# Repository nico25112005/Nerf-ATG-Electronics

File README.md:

# Nerf-ATG-Electronics

This repository contains the electronic design files for a custom printed circuit board (PCB) developed to enhance Nerf LaserOps blasters. The board utilizes an ESP32-S3 microcontroller to manage the blaster's functions and communicate via Bluetooth with a Unity application.

## Features

- Custom PCB design for Nerf LaserOps blasters
- ESP32-S3 microcontroller for improved performance and connectivity
- Bluetooth Classic for communication with a Unity application

## Installation

1. **PCB Assembly:**

   - Solder the components onto the board as per the schematic and Bill of Materials (BOM).

2. **Firmware Flashing:**

   - Flash the firmware onto the ESP32-S3. The firmware can be found in the Nerf-ATG-Firmware repository.

3. **Integration:**

   - Replace the original mainboard in the Nerf LaserOps blaster with the custom PCB.

4. **Unity App Setup:**

   - Install the Unity app from the Nerf-ATG-App repository on your device.
   - Pair the blaster with the app via Bluetooth.

## Usage

1. **Power On:**

   - Turn on the blaster.

2. **Connect to App:**

   - Open the Unity app and connect to the blaster via Bluetooth.

3. **Operation:**

   - Use the app to control and monitor the blaster’s functions.

## Contributing

Contributions are welcome! We are currently seeking assistance with programming the ESP32. If you have experience with ESP32 development, please consider contributing to the Nerf-ATG-Firmware repository. Please fork the repository and submit a pull request with your changes.

## Contact

For questions or support, please contact nico25112005.

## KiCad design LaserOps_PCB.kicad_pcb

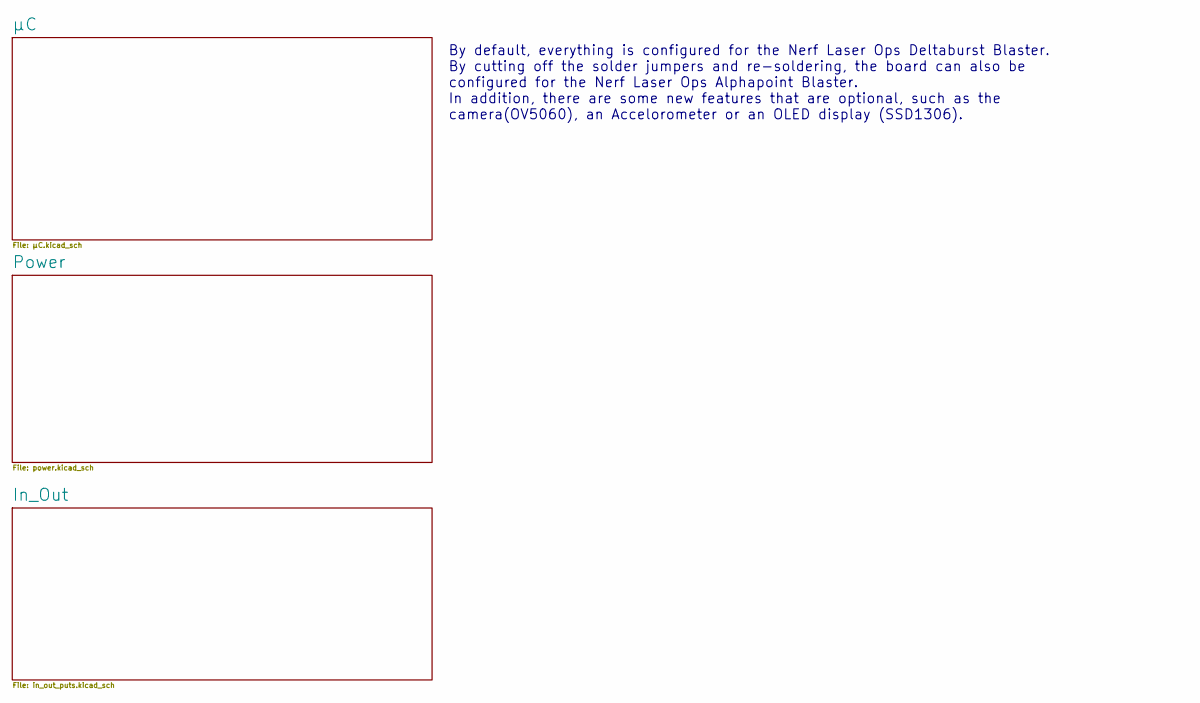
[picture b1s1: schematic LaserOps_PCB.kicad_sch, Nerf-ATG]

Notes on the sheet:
By default, everything is configured for the Nerf Laser Ops Deltaburst Blaster. By cutting off the solder jumpers and re-soldering, the board can also be configured for the Nerf Laser Ops Alphapoint Blaster. In addition, there are some new features that are optional, such as the camera(OV5060), an 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

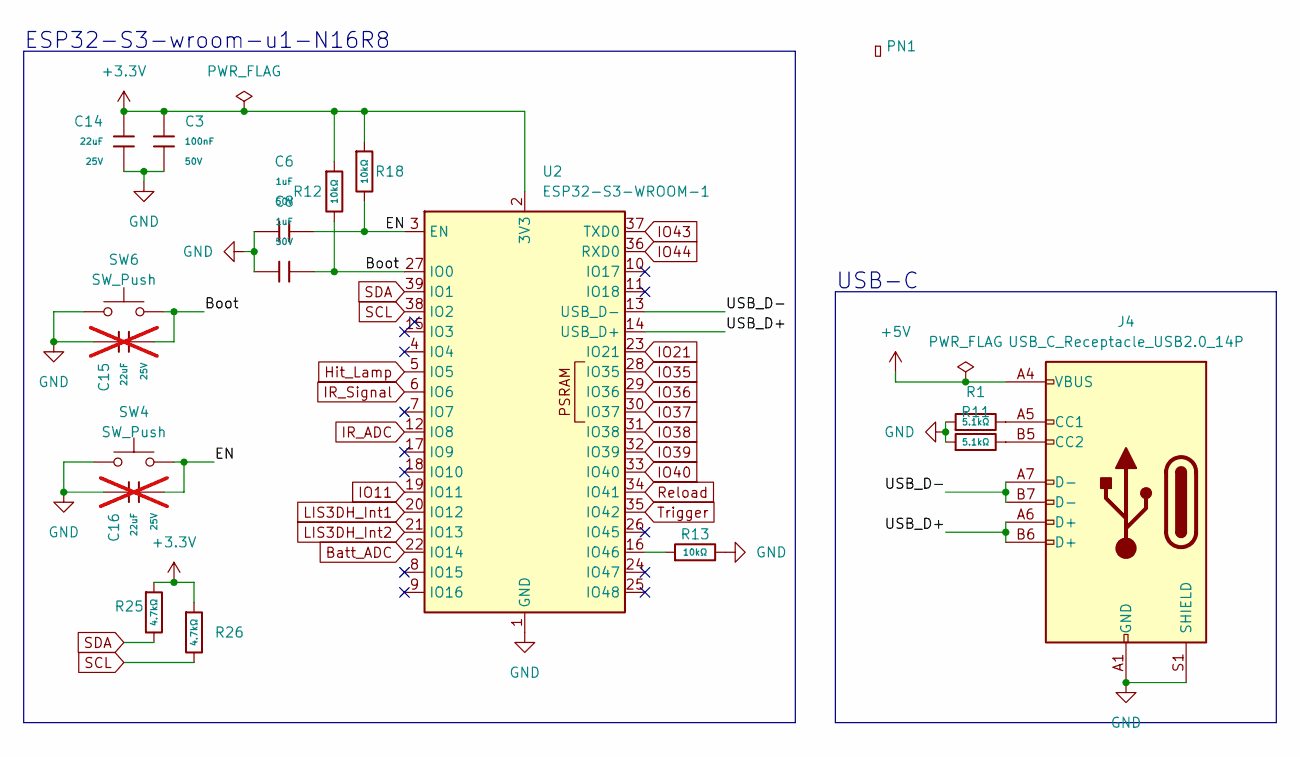
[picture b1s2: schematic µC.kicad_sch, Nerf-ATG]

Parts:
C3: 100nF; C_0805; Voltage Rated 50V; Tolerance ±10%; Part CC0805KRX7R9BB104; LCSC C49678
C6, C8: 1uF; C_0805; Voltage Rated 50V; Tolerance ±10%; Part CL21B105KBFNNNE; LCSC C28323
C14: 22uF; C_0805; Voltage Rated 25V; Tolerance ±20%; Part CL21A226MAQNNNE; LCSC C45783
C15, C16: 22uF; C_0805; Voltage Rated 25V; Tolerance ±20%; Part CL21A226MAQNNNE; LCSC C45783; not fitted
J4: USB_C_Receptacle_USB2.0_14P; USB_C_Receptacle_GCT_USB4085
PN1: Part_Num_JLCPCB
R1, R11: 5.1kΩ; R_0805; Overload Voltage (Max) 150V; Tolerance ±1%; Part 0805W8F5101T5E; LCSC C27834
R12, R13, R18: 10kΩ; R_0805; Overload Voltage (Max) 150V; Tolerance ±1%; Part 0805W8F1002T5E; LCSC C17414
R25, R26: 4.7kΩ; R_0805; Overload Voltage (Max) 150V; Tolerance ±1%; Part 0805W8F4701T5E; LCSC C17673
SW4, SW6: SW_Push; SW_SPST_CK_RS282G05A3
U2: ESP32-S3-WROOM-1

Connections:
+3.3V: C3.1, C14.1, R12.1, R18.1, R25.1, R26.1, U2.2 (3V3); also elsewhere on the board
+5V: J4.A4 (VBUS), J4.A9 (VBUS), J4.B4 (VBUS), J4.B9 (VBUS); also elsewhere on the board
/µC/Boot: C8.2, C15.2, R12.2, SW6.2, U2.27 (IO0)
/µC/EN: C6.2, C16.2, R18.2, SW4.2, U2.3 (EN)
/µC/USB_D+: J4.A6 (D+), J4.B6 (D+), U2.14 (USB_D+)
/µC/USB_D-: J4.A7 (D-), J4.B7 (D-), U2.13 (USB_D-)
Batt_ADC: U2.22 (IO14); also elsewhere on the board
GND: C3.2, C6.1, C8.1, C14.2, C15.1, C16.1, J4.A1 (GND), J4.A12 (GND), J4.B1 (GND), J4.B12 (GND), J4.S1 (SHIELD), R1.1, R11.1, R13.2, SW4.1, SW6.1, U2.1 (GND), U2.40 (GND), U2.41 (GND); also elsewhere on the board
Hit_Lamp: U2.5 (IO5); also elsewhere on the board
IO11: U2.19 (IO11); also elsewhere on the board
IO21: U2.23 (IO21); also elsewhere on the board
IO35: U2.28 (IO35); also elsewhere on the board
IO36: U2.29 (IO36); also elsewhere on the board
IO37: U2.30 (IO37); also elsewhere on the board
IO38: U2.31 (IO38); also elsewhere on the board
IO39: U2.32 (IO39); also elsewhere on the board
IO40: U2.33 (IO40); also elsewhere on the board
IO43: U2.37 (TXD0); also elsewhere on the board
IO44: U2.36 (RXD0); also elsewhere on the board
IR_ADC: U2.12 (IO8); also elsewhere on the board
IR_Signal: U2.6 (IO6); also elsewhere on the board
LIS3DH_Int1: U2.20 (IO12); also elsewhere on the board
LIS3DH_Int2: U2.21 (IO13); also elsewhere on the board
unnamed: J4.A5 (CC1), R1.2
unnamed: J4.B5 (CC2), R11.2
unnamed: R13.1, U2.16 (IO46)
Reload: U2.34 (IO41); also elsewhere on the board
SCL: R26.2, U2.38 (IO2); also elsewhere on the board
SDA: R25.2, U2.39 (IO1); also elsewhere on the board
Trigger: U2.35 (IO42); also elsewhere on the board

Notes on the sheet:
ESP32-S3-wroom-u1-N16R8
USB-C

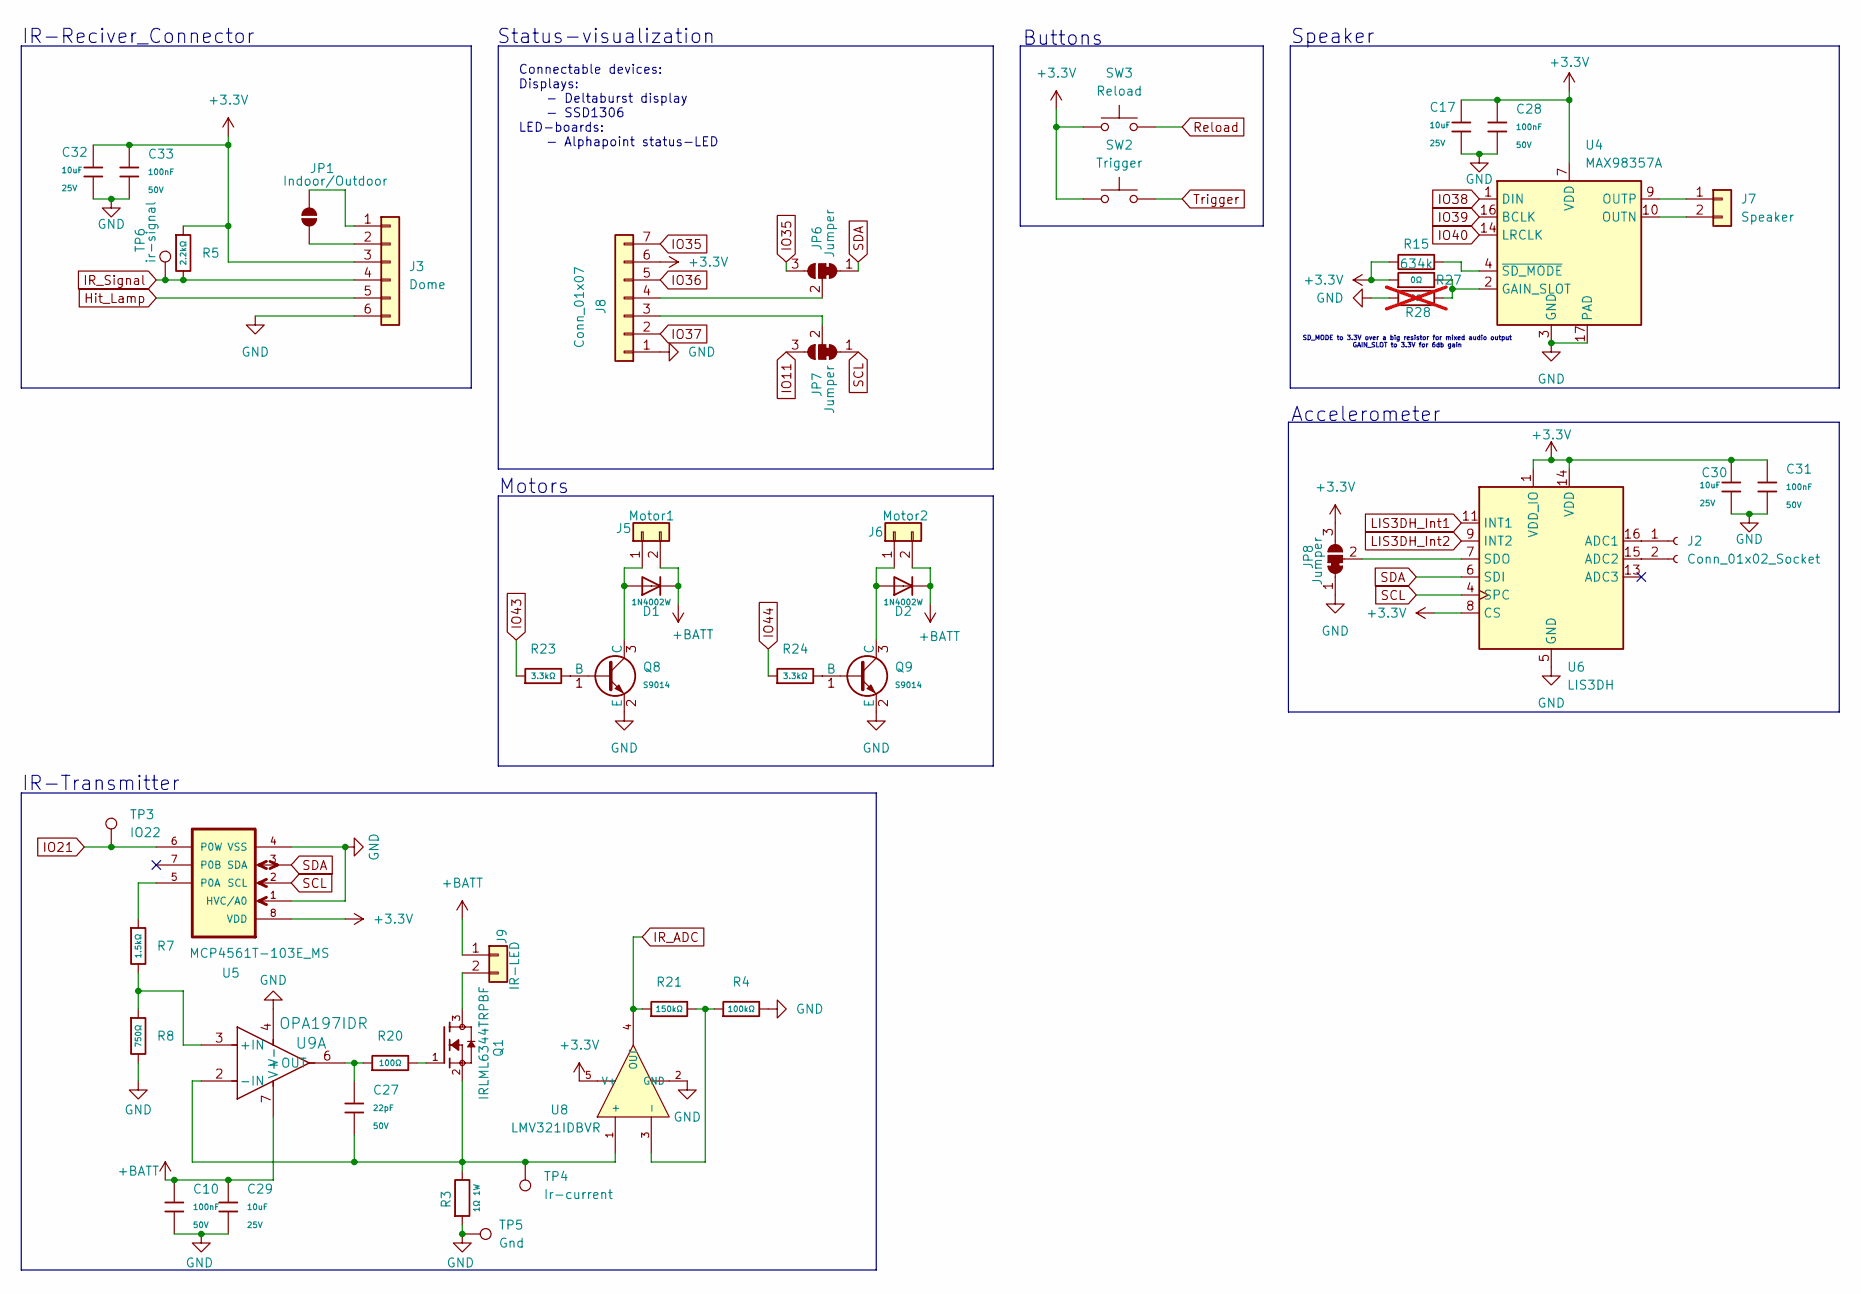
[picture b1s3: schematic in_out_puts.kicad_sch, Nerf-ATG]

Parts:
C10, C28, C31, C33: 100nF; C_0805; Voltage Rated 50V; Tolerance ±10%; Part CC0805KRX7R9BB104; LCSC C49678
C17, C29, C30, C32: 10uF; C_0805; Voltage Rated 25V; Tolerance ±10%; Part CL21A106KAYNNNE; LCSC C15850
C27: 22pF; C_0805; Voltage Rated 50V; Tolerance ±5%; Part CL21C220JBANNNC; LCSC C1804
D1, D2: 1N4002W; D_SOD-123FL; Forward Voltage (Vf@If) 1V@1.0A; Reverse Voltage (Vr) 100V; Part 1N4002W; LCSC C18199086
J2: Conn_01x02_Socket; PinHeader_1x02_P2.54mm_Vertical
J3: Dome; JST_PH_B6B-PH-SM4-TB_1x06-1MP_P2.00mm_Vertical
J5: Motor1; JST_PH_B2B-PH-SM4-TB_1x02-1MP_P2.00mm_Vertical
J6: Motor2; JST_PH_B2B-PH-SM4-TB_1x02-1MP_P2.00mm_Vertical
J7: Speaker; JST_PH_B2B-PH-SM4-TB_1x02-1MP_P2.00mm_Vertical
J8: Conn_01x07; JST_PH_S7B-PH-SM4-TB_1x07-1MP_P2.00mm_Horizontal
J9: IR-LED; PinHeader_1x02_P2.54mm_Vertical
JP1: Indoor/Outdoor; SolderJumper-2_P1.3mm_Open_RoundedPad1.0x1.5mm
JP6, JP7, JP8: Jumper; SolderJumper-3_P1.3mm_Bridged12_RoundedPad1.0x1.5mm_NumberL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
Q1: IRLML6344TRPBF; TRANS_IRLML6344TRPBF; PARTREV December 19, 2014
Q8, Q9: S9014; Q_SOT-23; Part S9014; LCSC C20069130
R3: 1Ω 1W; R_2512_6332Metric_Pad1.40x3.35mm_HandSolder
R4: 100kΩ; R_0805; Overload Voltage (Max) 150V; Tolerance ±1%; Part 0805W8F1003T5E; LCSC C149504
R5: 2.2kΩ; R_0805; Overload Voltage (Max) 150V; Tolerance ±1%; Part 0805W8F2201T5E; LCSC C17520
R7: 1.5kΩ; R_0805; Overload Voltage (Max) 150V; Tolerance ±1%; Part 0805W8F1501T5E; LCSC C4310
R8: 750Ω; R_0805; Overload Voltage (Max) 150V; Tolerance ±1%; Part 0805W8F7500T5E; LCSC C17818
R15: 634k; R_0805_2012Metric_Pad1.20x1.40mm_HandSolder
R20: 100Ω; R_0805; Overload Voltage (Max) 150V; Tolerance ±1%; Part 0805W8F1000T5E; LCSC C17408
R21: 150kΩ; R_0805; Overload Voltage (Max) 150V; Tolerance ±1%; Part 0805W8F1503T5E; LCSC C17470
R23, R24: 3.3kΩ; R_0805; Overload Voltage (Max) 150V; Tolerance ±1%; Part 0805W8F3301T5E; LCSC C26010
R27: 0Ω; R_0805; Overload Voltage (Max) 150V; Tolerance ±1%; Part 0805W8F0000T5E; LCSC C17477
R28: 0Ω; R_0805; Overload Voltage (Max) 150V; Tolerance ±1%; Part 0805W8F0000T5E; LCSC C17477; not fitted
SW2: Trigger; PinHeader_1x02_P2.54mm_Vertical
SW3: Reload; PinHeader_1x02_P2.54mm_Vertical
TP3: IO22; TestPoint_Pad_D1.5mm
TP4: Ir-current; TestPoint_Pad_D1.5mm
TP5: Gnd; TestPoint_Pad_D2.0mm
TP6: ir-signal; TestPoint_Pad_D1.5mm
U4: MAX98357A; TQFN-16-1EP_3x3mm_P0.5mm_EP1.23x1.23mm
U5: MCP4561T-103E_MS; SOP65P490X110-8N; MPN MCP4531T-103E/MS
U6: LIS3DH; LGA-16_3x3mm_P0.5mm_LayoutBorder3x5y
U8: LMV321IDBVR; SOT-23-5_L3.0-W1.7-P0.95-LS2.8-BR; Part LMV321IDBVR; LCSC C7972
U9: OPA197IDR; D0008A-IPC_A

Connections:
+3.3V: C17.1, C28.1, C30.1, C31.1, C32.1, C33.1, J3.3, J8.6, JP8.3 (B), R5.1, R15.1, R27.1, SW2.1, SW3.1, U4.7 (VDD), U4.8 (VDD), U5.8 (VDD), U6.1 (VDD_IO), U6.8 (CS), U6.14 (VDD), U8.5 (V+); also elsewhere on the board
+BATT: C10.1, C29.1, D1.1, D2.1, J5.2, J6.2, J9.1, U9.7 (V+); also elsewhere on the board
GND: C10.2, C17.2, C28.2, C29.2, C30.2, C31.2, C32.2, C33.2, J3.6, J8.1, JP8.1 (A), Q8.2 (E), Q9.2 (E), R3.2, R4.2, R8.2, R28.1, TP5.1, U4.3 (GND), U4.11 (GND), U4.15 (GND), U4.17 (PAD), U5.1 (HVC/A0), U5.4 (VSS), U6.5 (GND), U6.10 (GND), U6.12 (GND), U8.2 (GND), U9.4 (V-); also elsewhere on the board
Hit_Lamp: J3.5; also elsewhere on the board
IO11: JP7.3 (B); also elsewhere on the board
IO21: TP3.1, U5.6 (P0W); also elsewhere on the board
IO35: J8.7, JP6.3 (B); also elsewhere on the board
IO36: J8.5; also elsewhere on the board
IO37: J8.2; also elsewhere on the board
IO38: U4.1 (DIN); also elsewhere on the board
IO39: U4.16 (BCLK); also elsewhere on the board
IO40: U4.14 (LRCLK); also elsewhere on the board
IO43: R23.1; also elsewhere on the board
IO44: R24.1; also elsewhere on the board
IR_ADC: R21.1, U8.4 (OUT); also elsewhere on the board
IR_Signal: J3.4, R5.2, TP6.1; also elsewhere on the board
LIS3DH_Int1: U6.11 (INT1); also elsewhere on the board
LIS3DH_Int2: U6.9 (INT2); also elsewhere on the board
unnamed: J2.1, U6.16 (ADC1)
unnamed: J2.2, U6.15 (ADC2)
unnamed: J3.1, JP1.2 (B)
unnamed: J3.2, JP1.1 (A)
unnamed: D1.2, J5.1, Q8.3 (C)
unnamed: D2.2, J6.1, Q9.3 (C)
unnamed: J7.1, U4.9 (OUTP)
unnamed: J7.2, U4.10 (OUTN)
unnamed: J8.3, JP7.2 (C)
unnamed: J8.4, JP6.2 (C)
unnamed: J9.2, Q1.3
unnamed: JP8.2 (C), U6.7 (SDO)
unnamed: Q1.1, R20.2
unnamed: Q8.1 (B), R23.2
unnamed: Q9.1 (B), R24.2
unnamed: R27.2, R28.2, U4.2 (GAIN_SLOT)
unnamed: R15.2, U4.4 (~SD_MODE)
unnamed: R7.1, U5.5 (P0A)
unnamed: C27.2, Q1.2, R3.1, TP4.1, U8.1 (+), U9.2 (-IN)
unnamed: R4.1, R21.2, U8.3 (-)
unnamed: R7.2, R8.1, U9.3 (+IN)
unnamed: C27.1, R20.1, U9.6 (OUT)
Reload: SW3.2; also elsewhere on the board
SCL: JP7.1 (A), U5.2 (SCL), U6.4 (SPC); also elsewhere on the board
SDA: JP6.1 (A), U5.3 (SDA), U6.6 (SDI); also elsewhere on the board
Trigger: SW2.2; also elsewhere on the board

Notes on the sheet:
Status-visualization
IR-Transmitter
Connectable devices: Displays: - Deltaburst display - SSD1306 LED-boards: - Alphapoint status-LED
Speaker
SD_MODE to 3.3V over a big resistor for mixed audio output GAIN_SLOT to 3.3V for 6db gain
Buttons
Accelerometer
IR-Reciver_Connector
Motors

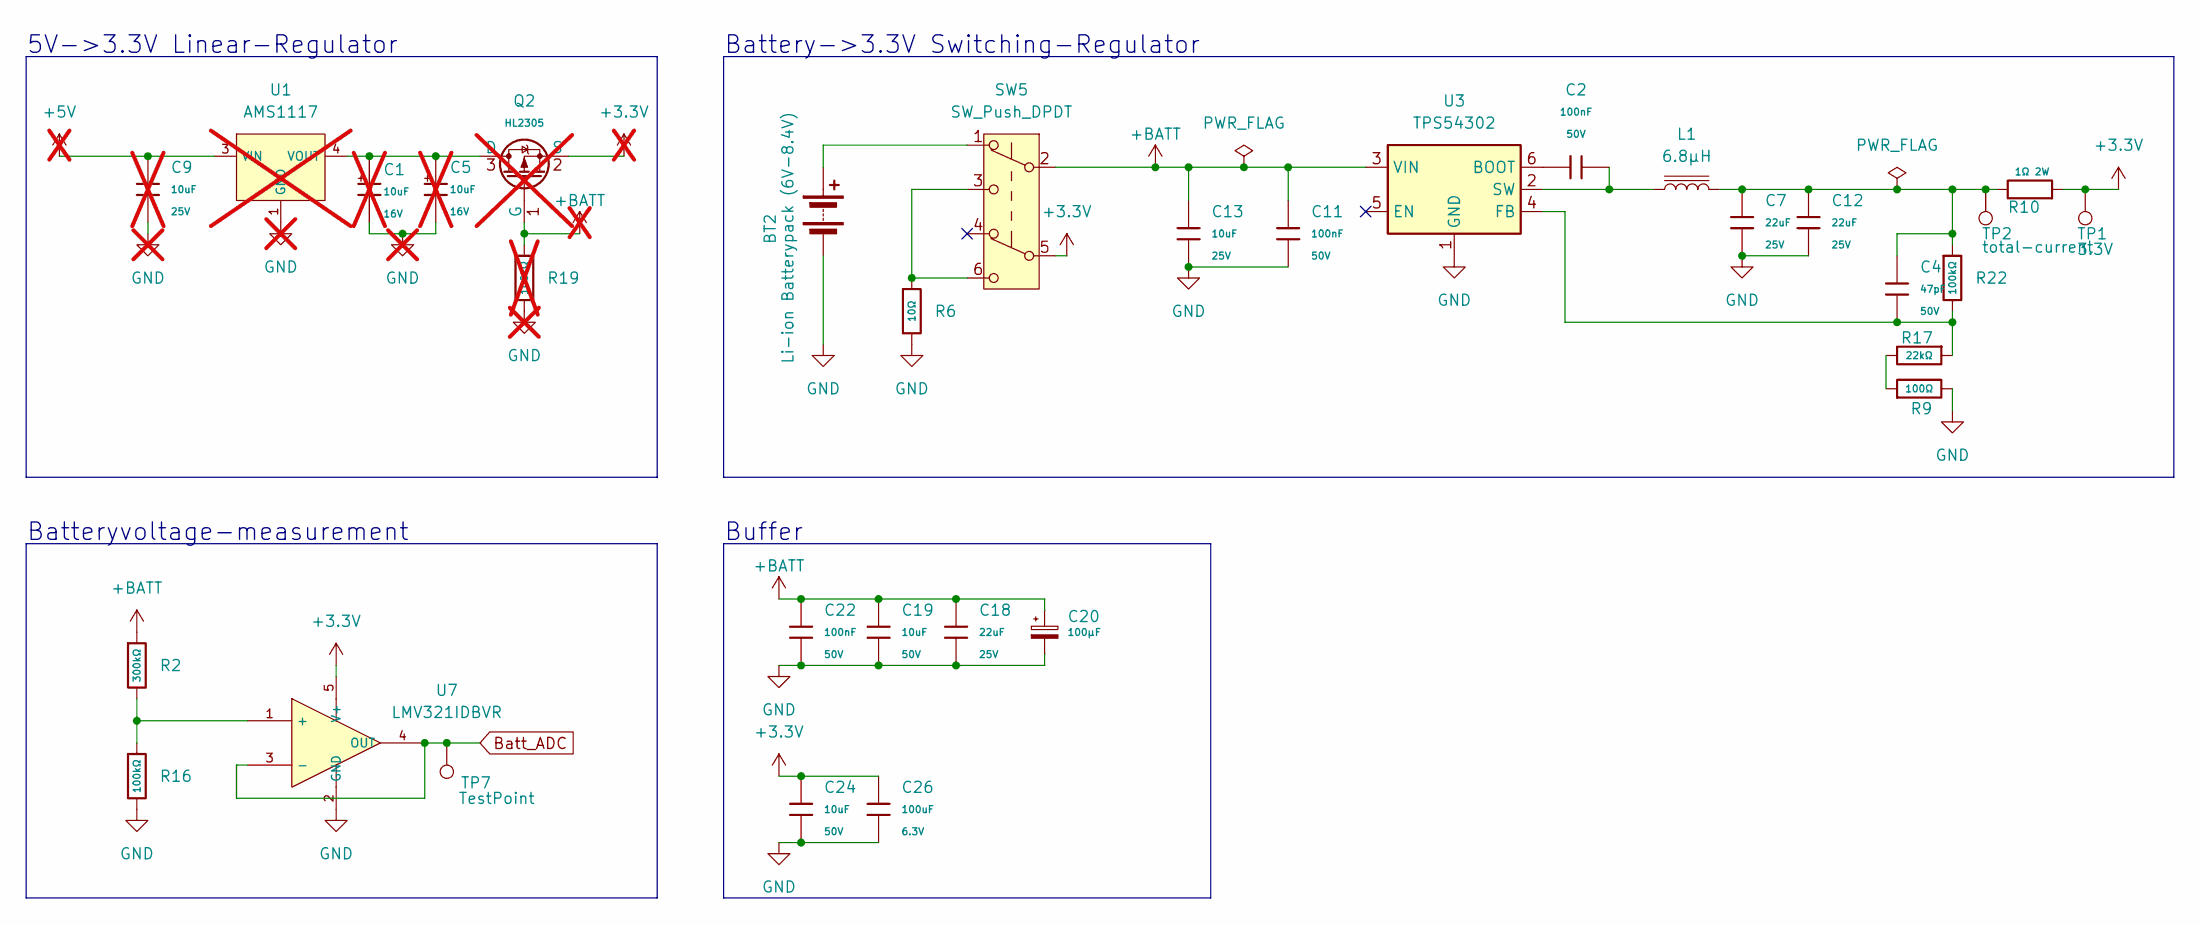
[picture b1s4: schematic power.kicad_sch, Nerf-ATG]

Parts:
BT2: Li-ion Batterypack (6V-8.4V); PinHeader_1x02_P2.54mm_Vertical
C1, C5: 10uF; C_CASE-A-3216-18(mm); Tolerance ±10%; Rated Voltage 16V; Part TAJA106K016RNJ; LCSC C7171; not fitted
C2, C11: 100nF; C_0805; Voltage Rated 50V; Tolerance ±10%; Part CC0805KRX7R9BB104; LCSC C49678
C4: 47pF; C_0805; Voltage Rated 50V; Tolerance ±5%; Part CL21C470JBANNNC; LCSC C14857
C7, C12: 22uF; C_0805; Voltage Rated 25V; Tolerance ±20%; Part CL21A226MAQNNNE; LCSC C45783
C9: 10uF; C_0805; Voltage Rated 25V; Tolerance ±10%; Part CL21A106KAYNNNE; LCSC C15850; not fitted
C13: 10uF; C_0805; Voltage Rated 25V; Tolerance ±10%; Part CL21A106KAYNNNE; LCSC C15850
C18: 22uF; C_1206; Voltage Rated 25V; Tolerance ±10%; Part CL31A226KAHNNNE; LCSC C12891
C19, C24: 10uF; C_1206; Voltage Rated 50V; Tolerance ±10%; Part CL31A106KBHNNNE; LCSC C13585
C20: 100µF; CP_Radial_D5.0mm_P2.50mm
C22: 100nF; C_1206; Voltage Rated 50V; Tolerance ±10%; Part CL31B104KBCNNNC; LCSC C24497
C26: 100uF; C_1206; Voltage Rated 6.3V; Tolerance ±20%; Part CL31A107MQHNNNE; LCSC C15008
L1: 6.8µH; L_Coilcraft_LPS4018
Q2: HL2305; Q_SOT-23; Part HL2305; LCSC C28646261; not fitted
R2: 300kΩ; R_0805; Overload Voltage (Max) 150V; Tolerance ±1%; Part 0805W8F3003T5E; LCSC C17616
R6: 10Ω; R_0805; Overload Voltage (Max) 150V; Tolerance ±1%; Part 0805W8F100JT5E; LCSC C17415
R9: 100Ω; R_0805; Overload Voltage (Max) 150V; Tolerance ±1%; Part 0805W8F1000T5E; LCSC C17408
R10: 1Ω 2W; R_2512_6332Metric_Pad1.40x3.35mm_HandSolder
R16, R22: 100kΩ; R_0805; Overload Voltage (Max) 150V; Tolerance ±1%; Part 0805W8F1003T5E; LCSC C149504
R17: 22kΩ; R_0805; Overload Voltage (Max) 150V; Tolerance ±1%; Part 0805W8F2202T5E; LCSC C17560
R19: 100kΩ; R_0805; Overload Voltage (Max) 150V; Tolerance ±1%; Part 0805W8F1003T5E; LCSC C149504; not fitted
SW5: SW_Push_DPDT; MHPS2266
TP1: 3.3V; TestPoint_Pad_D2.0mm
TP2: total-current; TestPoint_Pad_D1.5mm
TP7: TestPoint; TestPoint_Pad_D1.5mm
U1: AMS1117; SOT-223-3_L6.5-W3.4-P2.30-LS7.0-BR; Output Voltage 3.3V; Dropout Voltage 1.3V@(800mA); Part AMS1117-3.3; LCSC C6186; not fitted
U3: TPS54302; SOT-23-6
U7: LMV321IDBVR; SOT-23-5_L3.0-W1.7-P0.95-LS2.8-BR; Part LMV321IDBVR; LCSC C7972

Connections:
+3.3V: C24.1, C26.1, Q2.2 (S), R10.2, SW5.5 (B), TP1.1, U7.5 (V+); also elsewhere on the board
+5V: C9.1, U1.3 (VIN); also elsewhere on the board
+BATT: C11.1, C13.1, C18.1, C19.1, C20.1, C22.1, Q2.1 (G), R2.1, R19.1, SW5.2 (B), U3.3 (VIN); also elsewhere on the board
Batt_ADC: TP7.1, U7.3 (-), U7.4 (OUT); also elsewhere on the board
GND: BT2.2 (-), C1.2, C5.2, C7.2, C9.2, C11.2, C12.2, C13.2, C18.2, C19.2, C20.2, C22.2, C24.2, C26.2, R6.2, R9.2, R16.2, R19.2, U1.1 (GND), U3.1 (GND), U7.2 (GND); also elsewhere on the board
unnamed: BT2.1 (+), SW5.1 (A)
unnamed: C4.2, C7.1, C12.1, L1.2, R10.1, R22.1, TP2.1
unnamed: C1.1, C5.1, Q2.3 (D), U1.2 (VOUT), U1.4 (VOUT)
unnamed: R6.1, SW5.3 (C), SW5.6 (C)
unnamed: R9.1, R17.2
unnamed: C2.1, U3.6 (BOOT)
unnamed: C4.1, R17.1, R22.2, U3.4 (FB)
unnamed: C2.2, L1.1, U3.2 (SW)
unnamed: R2.2, R16.1, U7.1 (+)

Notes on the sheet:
Battery->3.3V Switching-Regulator
Buffer
5V->3.3V Linear-Regulator
Batteryvoltage-measurement

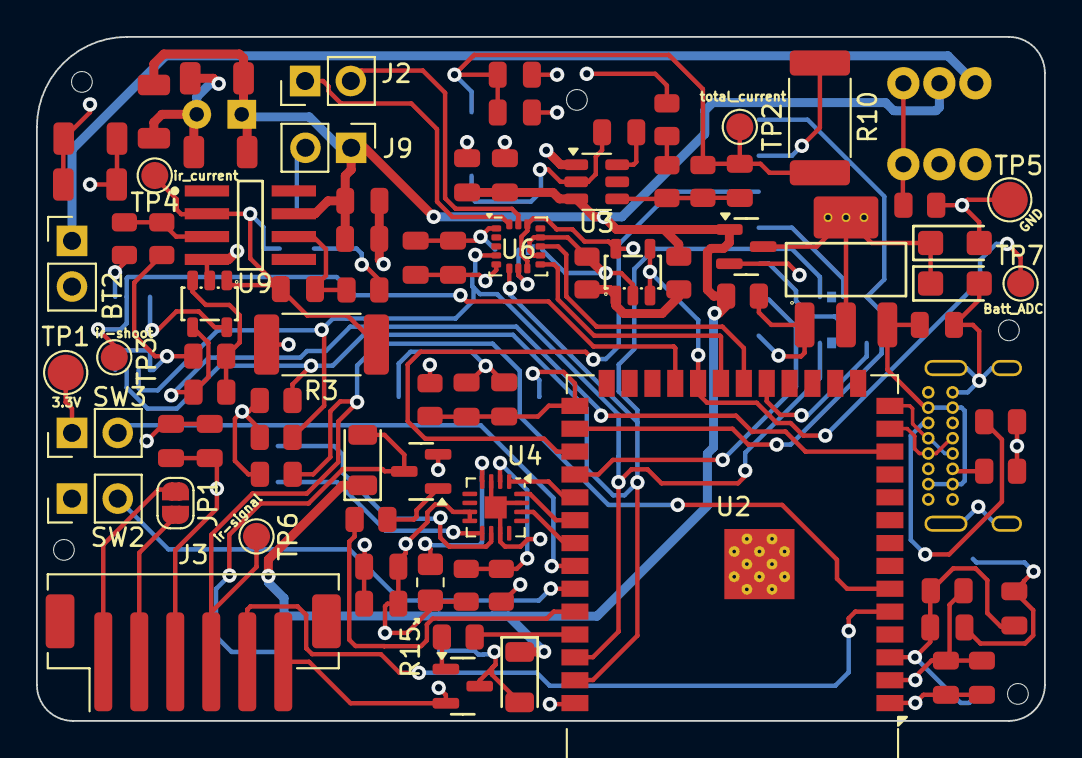
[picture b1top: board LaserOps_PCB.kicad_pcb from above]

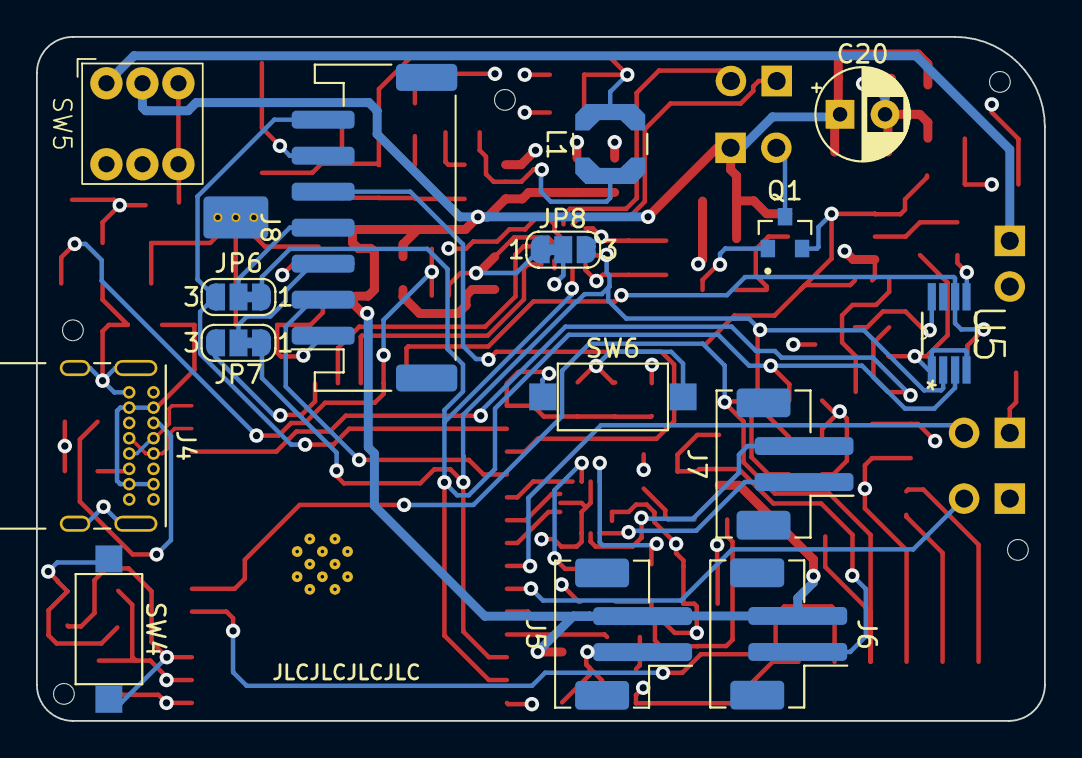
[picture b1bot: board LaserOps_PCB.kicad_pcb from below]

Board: 4 copper layers, 56.0 x 38.0 mm, 98 parts (16 on the bottom side), 61 nets.

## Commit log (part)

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2024-06-14 Update LICENSE
2024-06-14 init
2025-04-14 late night schmeatic with gotzi
2025-04-20 simulated IR-constant-current circuit, worked on schematic
2025-05-09 prepared for jlcpcb ordering.
2026-02-26 checked and fixed schematic, analized it with traceformer.io ai
2026-02-26 replaced ir-led constant current circuit
2026-02-26 pcb layout designing
2026-02-27 finished pcb design and routing
2026-02-27 finished pcb design and ordered first patch pcba (2pcs)
2026-03-19 pcb didn't commit correctly
